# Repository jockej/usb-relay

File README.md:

# usb-relay
A usb controlled relay

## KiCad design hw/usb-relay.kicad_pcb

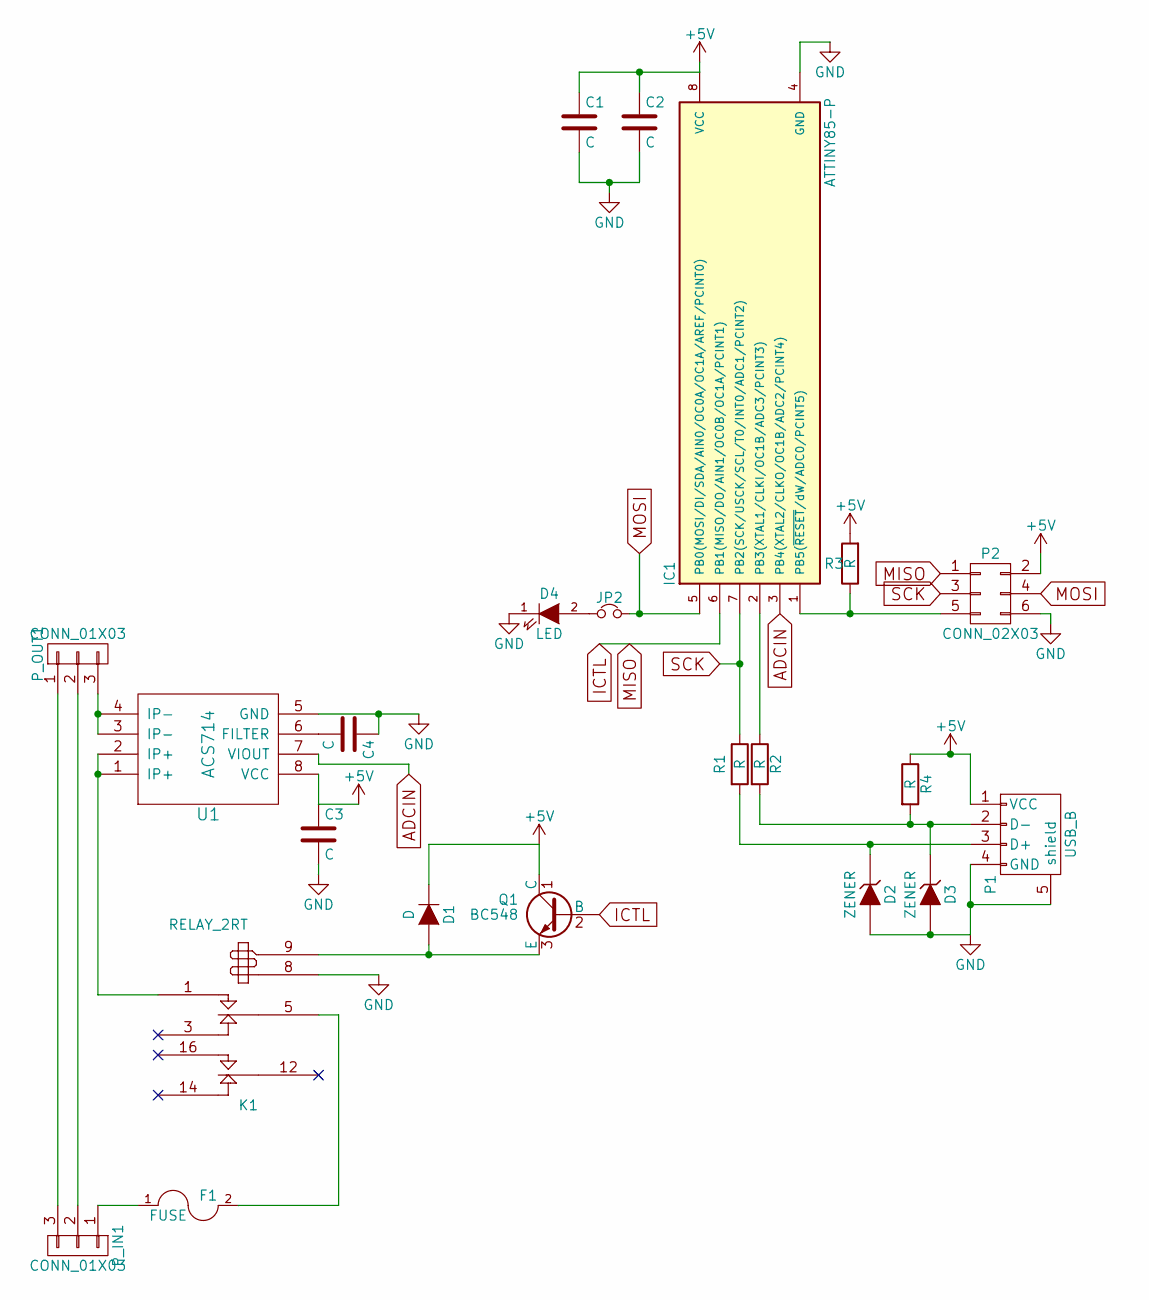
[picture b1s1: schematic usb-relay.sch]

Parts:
C1, C2, C3, C4: C; C_Disc_D3_P2.5
D1: D; Diode_DO-35_SOD27_Horizontal_RM10
D2, D3: ZENER; Diode_DO-35_SOD27_Horizontal_RM10
D4: LED; LED-5MM
F1: FUSE; Fuseholder5x20_horiz_open_inline_Type-I
IC1: ATTINY85-P; DIP-8_W7.62mm
JP2: Jumper_NC_Small; Pin_Header_Straight_1x02
K1: RELAY_2RT; Relay_DPDT_Schrack-RT2_RM5mm
P1: USB_B; USB_Micro-B
P2: CONN_02X03; Pin_Header_Straight_2x03
P_IN1: CONN_01X03; AK300-3
P_OUT1: CONN_01X03; AK300-3
Q1: BC548; TO-92_Inline_Narrow_Oval
R1, R2, R3, R4: R; Resistor_Horizontal_RM10mm
U1: ACS714; SOIC-8_3.9x4.9mm_Pitch1.27mm

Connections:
+5V: C1.1, C2.1, C3.1, D1.1 (K), IC1.8 (VCC), P1.1 (VCC), P2.2, Q1.1 (C), R3.2, R4.1, U1.8 (VCC)
ADCIN: IC1.3 (PB4(XTAL2/CLKO/OC1B/ADC2/PCINT4)), U1.7 (VIOUT)
GND: C1.2, C2.2, C3.2, C4.1, D2.2 (A), D3.2 (A), D4.1 (K), IC1.4 (GND), K1.8, P1.4 (GND), P1.5 (shield), P2.6, U1.5 (GND)
ICTL: IC1.6 (PB1(MISO/DO/AIN1/OC0B/OC1A/PCINT1)), P2.1, Q1.2 (B)
MOSI: IC1.5 (PB0(MOSI/DI/SDA/AIN0/OC0A/OC1A/AREF/PCI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), JP2.2, P2.4
unnamed: C4.2, U1.6 (FILTER)
unnamed: D1.2 (A), K1.9, Q1.3 (E)
unnamed: D2.1 (K), P1.3 (D+), R1.2
unnamed: D3.1 (K), P1.2 (D-), R2.2, R4.2
unnamed: D4.2 (A), JP2.1
unnamed: F1.1, P_IN1.1
unnamed: F1.2, K1.5 (C1)
unnamed: IC1.1 (PB5(~RESET~/dW/ADC0/PCINT5)), P2.5, R3.1
unnamed: IC1.2 (PB3(XTAL1/CLKI/OC1B/ADC3/PCINT3)), R2.1
unnamed: K1.1 (T1), U1.1 (IP+), U1.2 (IP+)
unnamed: P_IN1.2, P_OUT1.2
unnamed: P_IN1.3, P_OUT1.1
unnamed: P_OUT1.3, U1.3 (IP-), U1.4 (IP-)
SCK: IC1.7 (PB2(SCK/USCK/SCL/T0/INT0/ADC1/PCINT2)), P2.3, R1.1

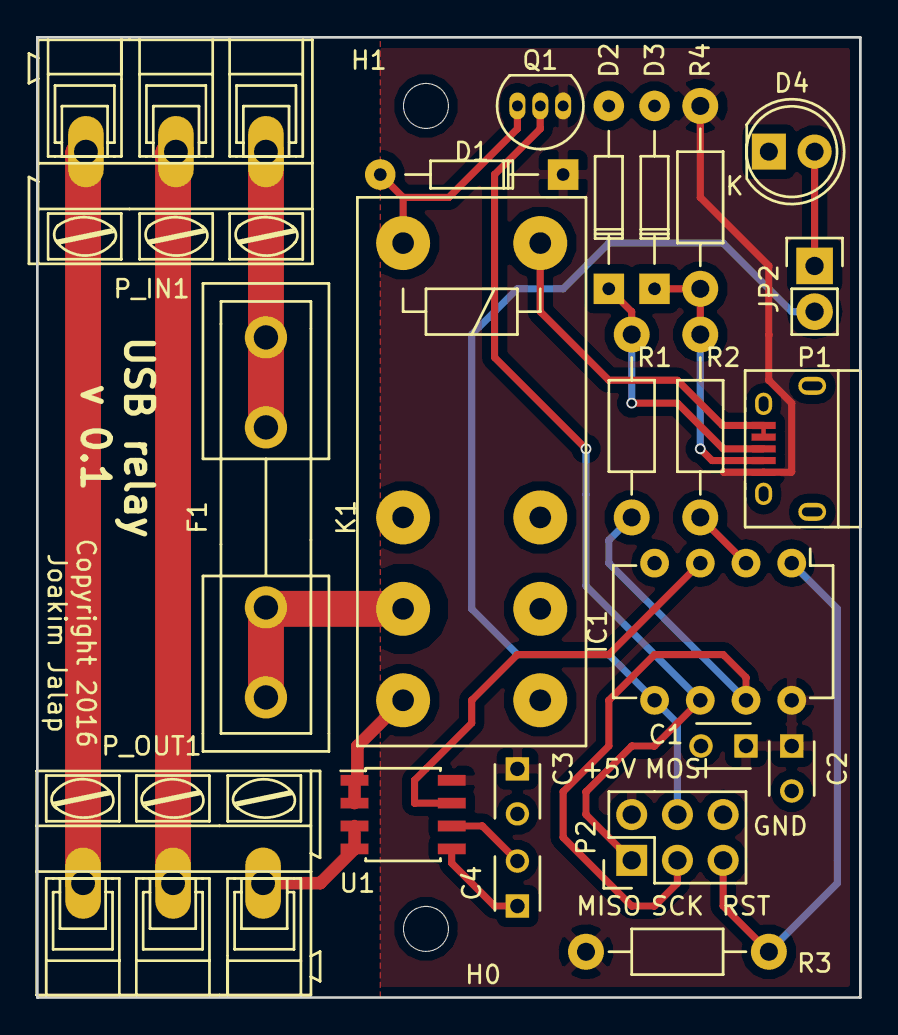
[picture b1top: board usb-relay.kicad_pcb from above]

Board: 2 copper layers, 45.7 x 53.3 mm, 24 parts (0 on the bottom side), 19 nets.

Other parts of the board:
H0, H1: MountingHole_2-5mm

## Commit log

2016-02-16 start on hw
2016-03-01 Almost done, needs component values
2016-03-01 Add a LED on MOSI pin, why not?
2016-03-04 Remove the reset jumper
2016-05-03 A change?

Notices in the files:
hw/usb-relay.kicad_pcb:
Copyright 2016
